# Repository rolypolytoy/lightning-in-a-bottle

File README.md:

# Lightning In A Bottle

Lightning in a bottle is an open-source, low-cost charge sensitive amplifier with several improvements over all existing commercial designs.

It has a >2x lower cost, a 750x greater gain, >5x greater bandwidth, >50% lower cost, and sub-5 dB lower SNR. Importantly- its real SNR will be higher since the gain is >750x, and since ADCs have noise, our gain will basically reduce that noise by 750x, and **so in real systems our CSA will have a much higher SNR than Cremat's module**, and thus this has no real 'weakness'. It also uses standard +5V as its power source rather than the weird +-6V-13V supplies the Cremat module needs.

It also uses commercial off-the-shelf components and so can be more easily and cheaply scaled than the Cremat CR-113 and other modules, whose components are proprietary and who may not ship to every country in the world in a timely manner.

Components:
- LMH6629SD, an ultra-low noise Op-Amp
- TPS7A3301RGW for power regulation
- Several miscellaneous ceramic capacitors, SMD resistors, inductors, and other generic components.

You can use a typical RC-CR pulse shaper or buy one from Cremat (might replace it soon but the CR-200-500ns arrived, so I don't need to make another one), but the specs of that are less important than the CSA setup. CSAs are better than transimpedance amplifiers for electron detection and nuclear research.

The [Cremat CR-113's datasheet](https://www.cremat.com/CR-113-R2.1.pdf) shows 18k electrons RMS baseline noise, 1.3 mV/pC gain and 30 electrons of noise RMS per pF, which means for the 0.01 microfarad AC coupled capacitor they show in their datasheet means they'll have around 300,000 electrons RMS of noise- which is a LOT of noise. Our SNR?

Op-amp voltage noise is 0.69 nV/√Hz (LMH6629), our feedback capacitor: Cf = 1pF, our feedback resistor: Rf = 10MΩ, our bandwidth: f = 1/(2π × Rf × Cf) = 1/(2π × 10MOhm × 1pF) = 15.9 kHz. Voltage noise is 0.69 nV/√Hz × √(15,900 Hz) = 0.69nV * 126 = 87 nV RMS voltage noise. Our gain is 1/Cf = 1/(1pF) = 1e12 V/C = 1000 mV/pC which is 750 times their gain. Our charge noise is thus 87nV / (1V/pC) = 87fC RMS, which is ~543,000 electrons, which is about a ~5 dB difference. 

Schematic file looks like:

PCB file looks like:

Gerbers, BOM and all manufacturing information is already there, and the project is in KiCAD's native file formats. It's a normal four-layer PCB with an estimated BOM of around $50/unit, which is less than half the price of a Cremat CR-113 module. 

## Charge Sensitive Amplifiers
Here's my attempt at explaining what a charge sensitive amplifier, written as a dialectic for my amusement (because who has the time to write a datasheet?)

A charge sensitive amplifier is basically just a capacitor around an op-amp. A capacitor is a thing which has capacitance, whereas an op-amp is something which makes voltage go up. I've made an informative schematic to fully get the concept across.

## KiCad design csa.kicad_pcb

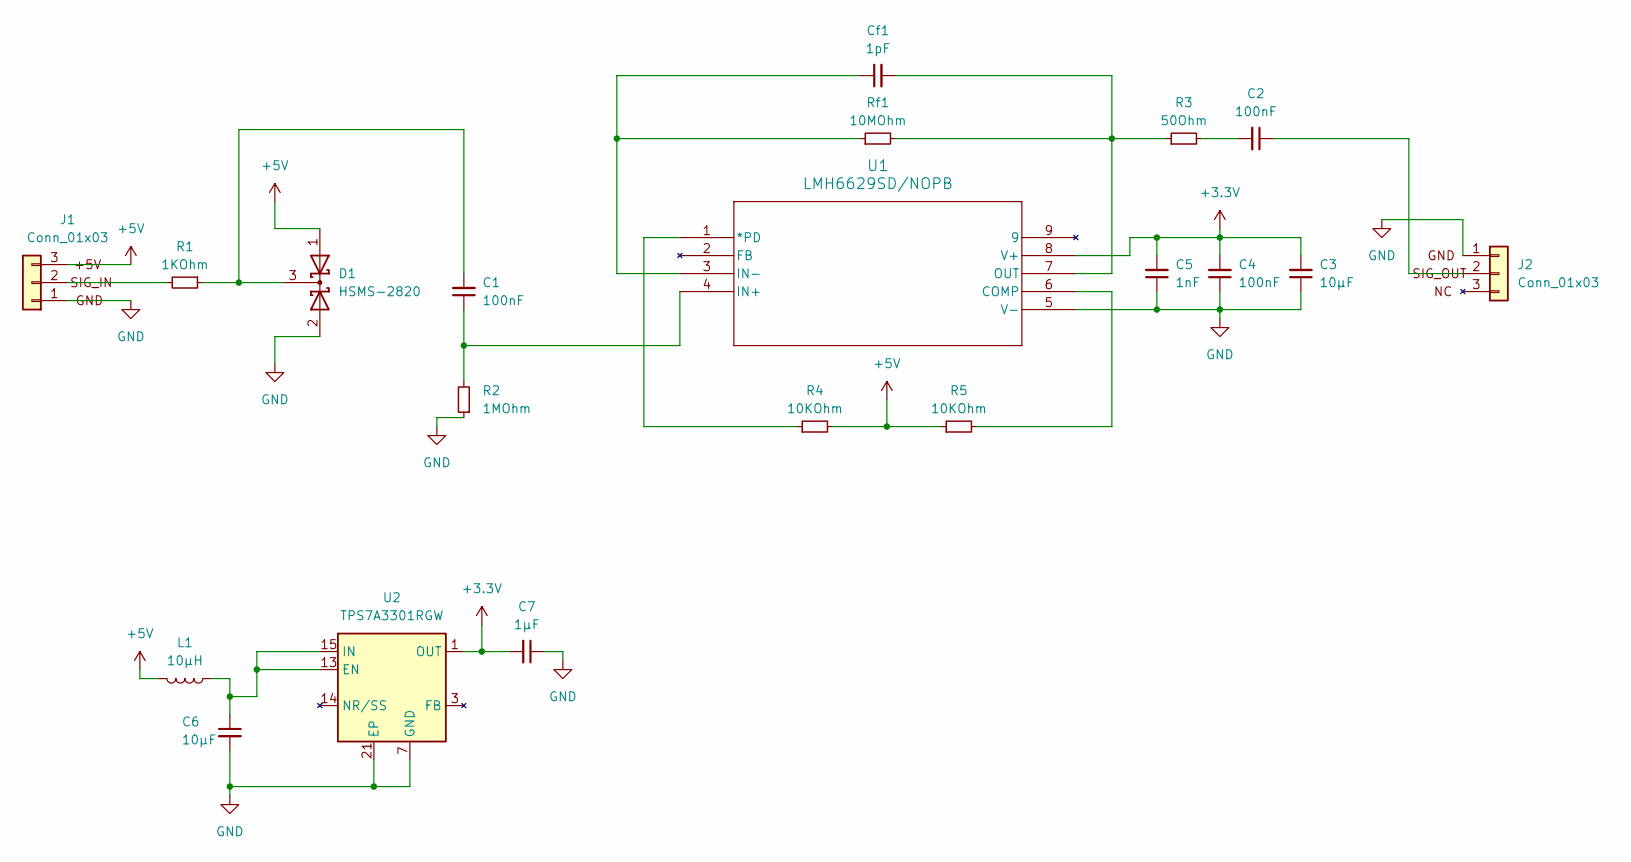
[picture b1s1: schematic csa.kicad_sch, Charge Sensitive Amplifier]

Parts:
C1, C2, C4: 100nF; C_0603_1608Metric
C3, C6: 10μF; C_1206_3216Metric
C5: 1nF; C_0603_1608Metric
C7: 1μF; C_0603_1608Metric
Cf1: 1pF; C_0603_1608Metric
D1: HSMS-2820; SOT-23
J1, J2: Conn_01x03; PinHeader_1x03_P2.54mm_Vertical
L1: 10μH; L_0805_2012Metric
R1: 1KOhm; R_0603_1608Metric
R2: 1MOhm; R_0603_1608Metric
R3: 50Ohm; R_0603_1608Metric
R4, R5: 10KOhm; R_0603_1608Metric
Rf1: 10MOhm; R_0805_2012Metric
U1: LMH6629SD/NOPB; WSON-8-1EP_3x3mm_P0.5mm_EP1.2x2mm
U2: TPS7A3301RGW; Texas_RGW0020A_VQFN-20-1EP_5x5mm_P0.65mm_EP3.15x3.15mm_Ther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

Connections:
+3.3V: C3.2, C4.2, C5.2, C7.2, U1.8 (V+), U2.1 (OUT), U2.20 (OUT)
+5V: D1.1 (A), J1.3, L1.2, R4.2, R5.1
GND: C3.1, C4.1, C5.1, C6.2, C7.1, D1.2 (A), J1.1, J2.1, R2.1, U1.5 (V-), U2.7 (GND), U2.21 (EP)
unnamed: C2.2, R3.2
unnamed: C1.2, D1.3 (K), R1.1
unnamed: J1.2, R1.2
unnamed: C2.1, J2.2
unnamed: R4.1, U1.1 (*PD)
unnamed: R5.2, U1.6 (COMP)
unnamed: C1.1, R2.2, U1.4 (IN+)
unnamed: Cf1.1, Rf1.1, U1.3 (IN-)
unnamed: Cf1.2, R3.1, Rf1.2, U1.7 (OUT)
unnamed: C6.1, L1.1, U2.13 (EN), U2.15 (IN), U2.16 (IN)

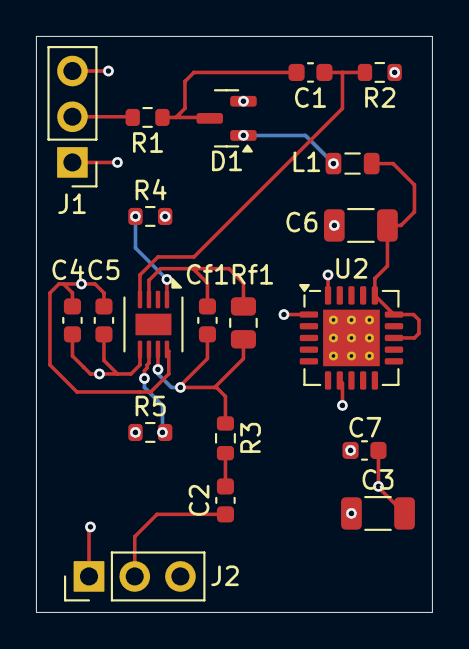
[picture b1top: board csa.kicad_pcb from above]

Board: 4 copper layers, 22.0 x 32.0 mm, 20 parts (0 on the bottom side), 13 nets.

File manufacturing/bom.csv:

"Id";"Designator";"Footprint";"Quantity";"Designation";"Supplier and ref";
1;"C1,C2,C4";"C_0603_1608Metric";3;"100nF";;;
2;"C3,C6";"C_1206_3216Metric";2;"10μF";;;
3;"U2";"Texas_RGW0020A_VQFN-20-1EP_5x5mm_P0.65mm_EP3.15x3.15mm_ThermalVias";1;"TPS7A3301RGW";;;
4;"C7";"C_0603_1608Metric";1;"1μF";;;
5;"Cf1";"C_0603_1608Metric";1;"1pF";;;
6;"U1";"WSON-8-1EP_3x3mm_P0.5mm_EP1.2x2mm";1;"LMH6629SD/NOPB";;;
7;"R4,R5";"R_0603_1608Metric";2;"10KOhm";;;
8;"Rf1";"R_0805_2012Metric";1;"10MOhm";;;
9;"C5";"C_0603_1608Metric";1;"1nF";;;
10;"J2,J1";"PinHeader_1x03_P2.54mm_Vertical";2;"Conn_01x03";;;
11;"R3";"R_0603_1608Metric";1;"50Ohm";;;
12;"D1";"SOT-23";1;"HSMS-2820";;;
13;"L1";"L_0805_2012Metric";1;"10μH";;;
14;"R2";"R_0603_1608Metric";1;"1MOhm";;;
15;"R1";"R_0603_1608Metric";1;"1KOhm";;;

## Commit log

2025-06-21 initial push
